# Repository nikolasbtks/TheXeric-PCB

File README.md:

# TheXeric-PCB

## Description

This project demonstrates a custom 2-layer PCB containing the ATmega-4809 microcontroller. This board can be used for embedded development applications using multiple peripherals.

## Components

1. Microcontroller: ATmega4809
   - 6 KB SRAM and 48 MB Flash
   - 20 MHz clock speed 
   
3. USB Connectivity:
   - USB Type-C for data and power 
   - USBLC6-2SC6 for ESD protection

4. Power Supply: LM3670MF-3.3 
   - Voltage regulator for stable 3.3V output
  
5. Headers:
   - UPDI header for debugging
   - GPIO, I2C, SPI and USART headers for external connections

6. Memory: AT24CS32-STUM
   - 32 Kbit of EEPROM storage
   - Non-volatile memory storage expansion

8. Sensor: TC1047xNB
   - Analog voltage output, propotional to temperature

## Disclaimer

This project is currently in **testing phase**. The provided documentation is shared for prototyping and learning purposes. If you choose to manufacture and use the board, please proceed with care, as it has not yet been fully validated.

## Schematic and PCB Design

The board was designed using KiCad. Files from the PCB design can be found in the **hardware** folder for board manufacture. This folder includes:

- PCB Schematic 
- PCB Layout
- Gerber files
- Assembly files

Below is a 3D render of the PCB design:

## How to Use

1. Power the board
   - Use a USB Type-C cable to power the board.
     
2. Microcontroller Programming:
   - Use Arduino IDE or any other platform to program the microcontroller.
   - Use a debugger with a UPDI header.

3. Peripheral Access
   - Use the GPIO, I2C, SPI and USART headers to connect peripherals.

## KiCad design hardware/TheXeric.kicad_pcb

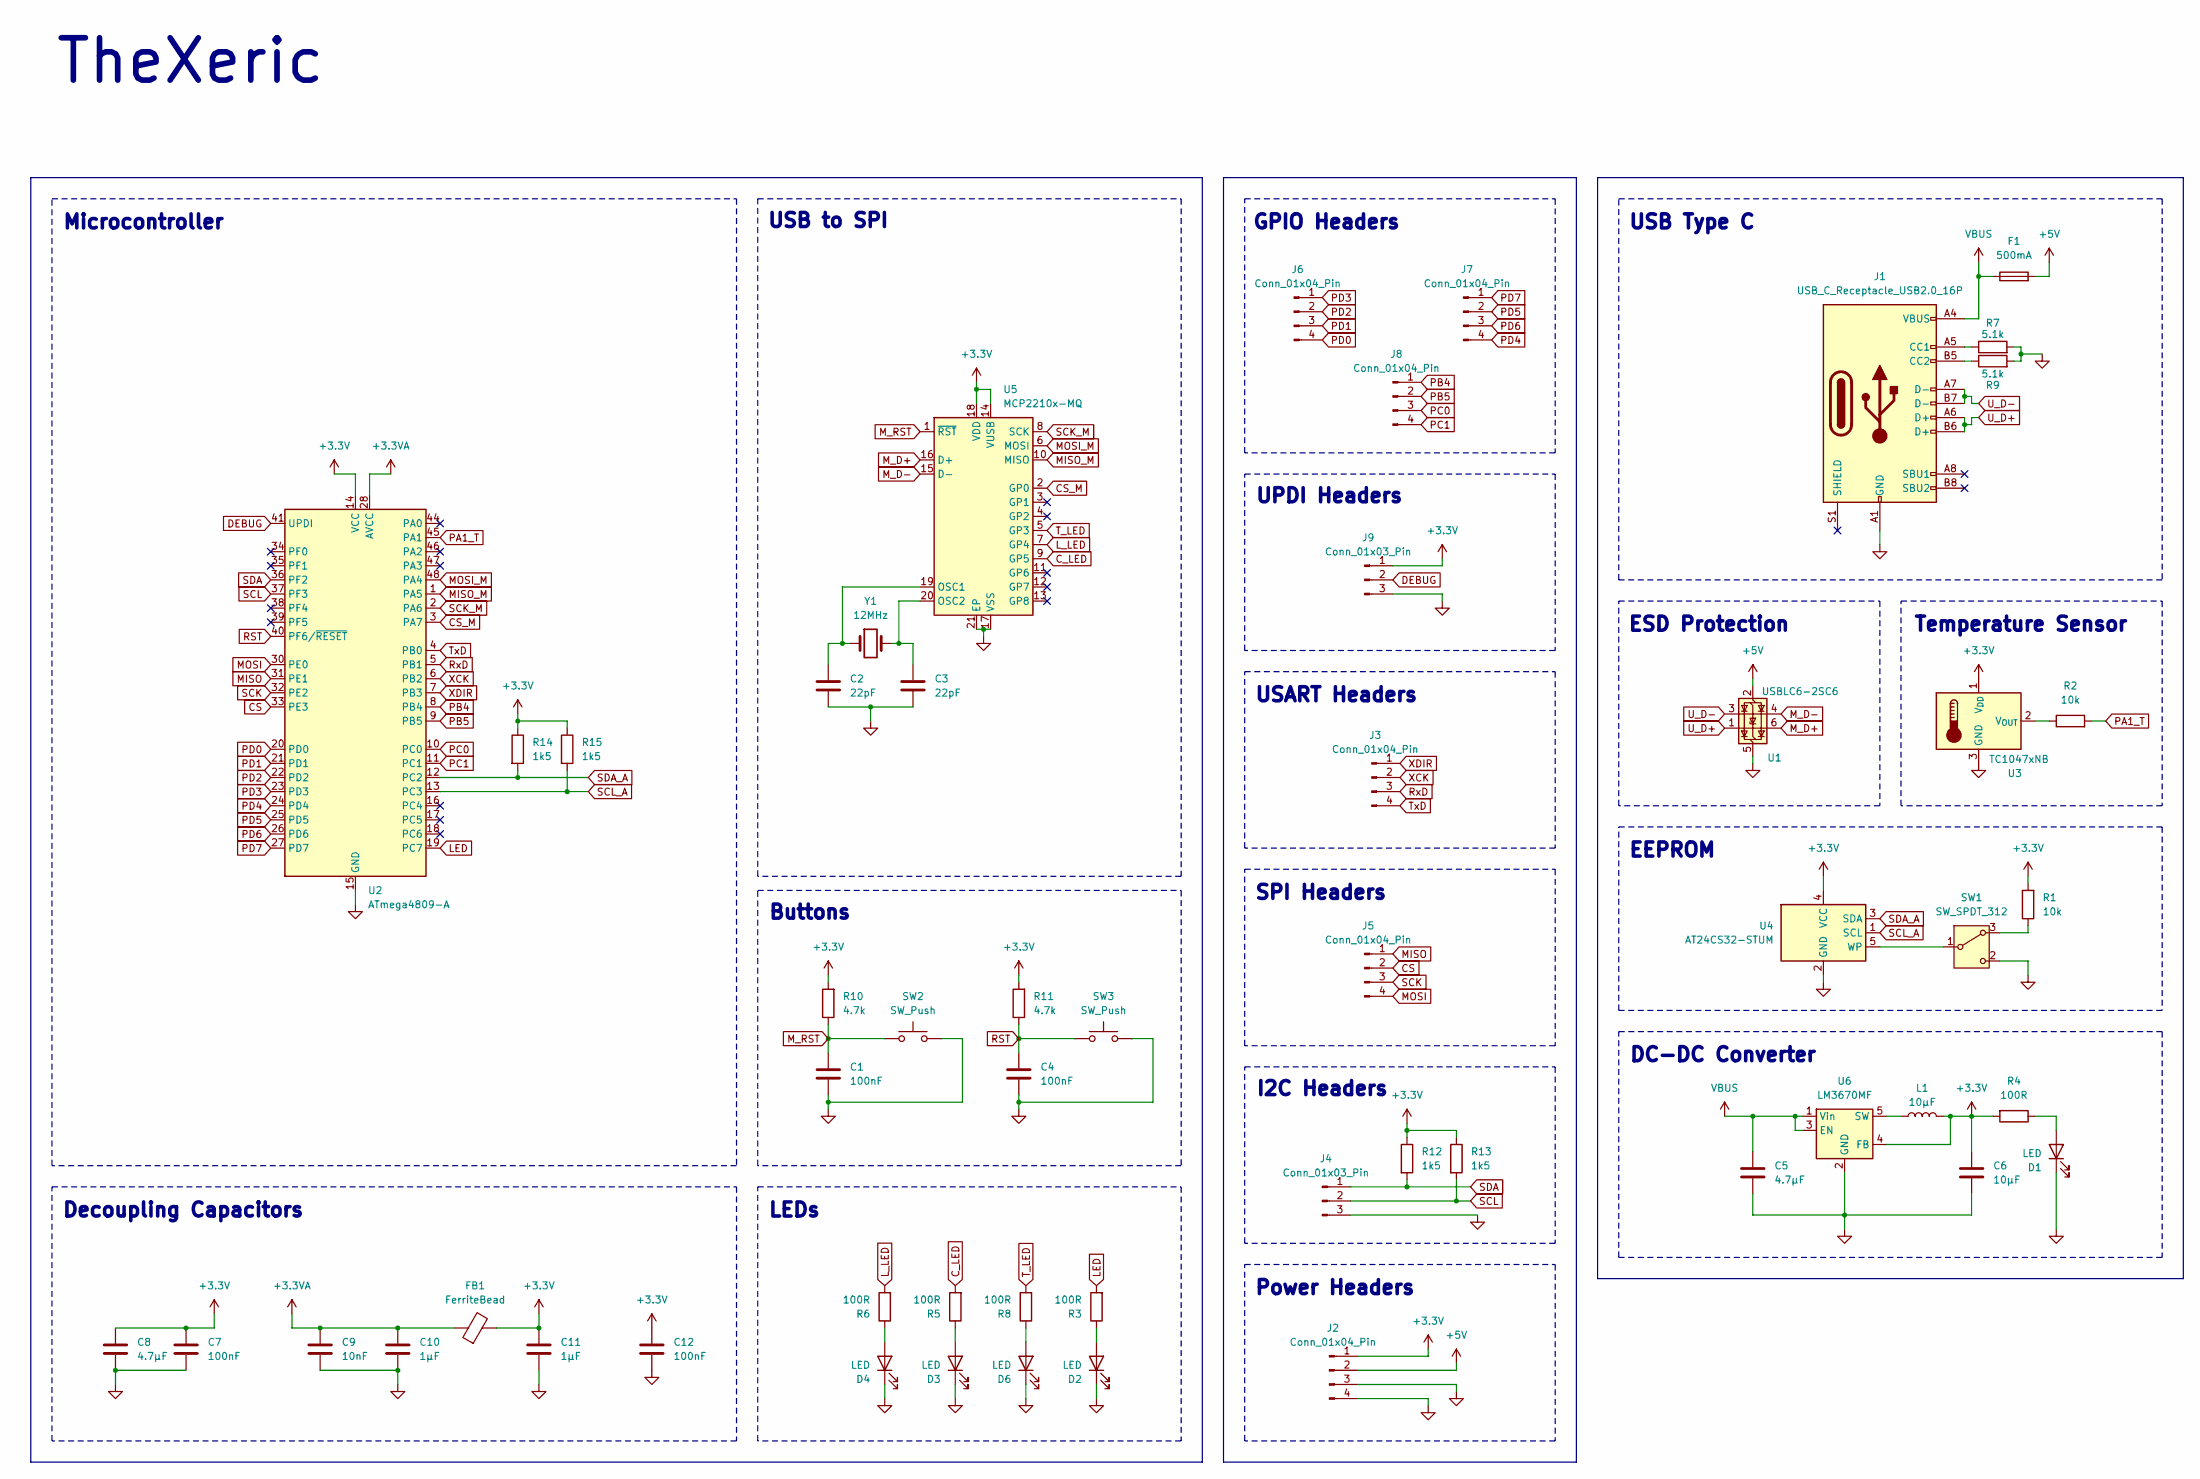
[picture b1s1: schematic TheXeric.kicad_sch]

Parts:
C1, C4, C7, C12: 100nF; C_0402_1005Metric
C2, C3: 22pF; C_0402_1005Metric
C5, C8: 4.7μF; C_0603_1608Metric
C6: 10μF; C_0603_1608Metric
C9: 10nF; C_0402_1005Metric
C10, C11: 1μF; C_0603_1608Metric
D1, D2, D3, D4, D6: LED; LED_0603_1608Metric
F1: 500mA; Fuse_0402_1005Metric
FB1: FerriteBead; L_0603_1608Metric
J1: USB_C_Receptacle_USB2.0_16P; USB_C_Receptacle_GCT_USB4105-xx-A_16P_TopMnt_Horizontal
J2, J3, J5, J6, J7, J8: Conn_01x04_Pin; PinHeader_1x04_P2.54mm_Vertical
J4, J9: Conn_01x03_Pin; PinHeader_1x03_P2.54mm_Vertical
L1: 10μF; L_0603_1608Metric
R1, R2: 10k; R_0402_1005Metric
R3, R4, R5, R6, R8: 100R; R_0603_1608Metric
R7, R9: 5.1k; R_0402_1005Metric
R10, R11: 4.7k; R_0402_1005Metric
R12, R13, R14, R15: 1k5; R_0402_1005Metric
SW1: SW_SPDT_312; SW_SPDT_PCM12
SW2, SW3: SW_Push; SW_SPST_B3U-1000P
U1: USBLC6-2SC6; SOT-23-6
U2: ATmega4809-A; TQFP-48_7x7mm_P0.5mm
U3: TC1047xNB; SOT-23
U4: AT24CS32-STUM; SOT-23-5
U5: MCP2210x-MQ; QFN-20-1EP_5x5mm_P0.65mm_EP3.35x3.35mm
U6: LM3670MF; TSOT-23-5
Y1: 12MHz; Crystal_SMD_3215-2Pin_3.2x1.5mm

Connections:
+3.3V: C6.1, C7.1, C8.1, C11.1, C12.1, FB1.2, J2.1, J9.1, L1.2, R1.2, R4.2, R10.2, R11.2, R12.1, R13.1, R14.1, R15.1, U2.14 (VCC), U2.42 (VCC), U3.1 (V_{DD}), U4.4 (VCC), U5.14 (VUSB), U5.18 (VDD), U6.4 (FB)
+3.3VA: C9.1, C10.1, FB1.1, U2.28 (AVCC)
+5V: F1.2, J2.2, U1.2 (GND)
CS: J5.2, U2.33 (PE3)
CS_M: U2.3 (PA7), U5.2 (GP0)
C_LED: R5.2, U5.9 (GP5)
DEBUG: J9.2, U2.41 (UPDI)
GND: C1.2, C2.2, C3.2, C4.2, C5.2, C6.2, C7.2, C8.2, C9.2, C10.2, C11.2, C12.2, D1.1 (K), D2.1 (K), D3.1 (K), D4.1 (K), D6.1 (K), J1.A1 (GND), J1.A12 (GND), J1.B1 (GND), J1.B12 (GND), J2.3, J2.4, J4.3, J9.3, R7.2, R9.2, SW1.2 (C), SW2.2, SW3.2, U1.5 (VBUS), U2.15 (GND), U2.29 (GND), U2.43 (GND), U3.3 (GND), U4.2 (GND), U5.17 (VSS), U5.21 (EP), U6.2 (GND)
LED: R3.2, U2.19 (PC7)
L_LED: R6.2, U5.7 (GP4)
MISO: J5.1, U2.31 (PE1)
MISO_M: U2.1 (PA5), U5.10 (MISO)
MOSI: J5.4, U2.30 (PE0)
MOSI_M: U2.48 (PA4), U5.6 (MOSI)
M_D+: U1.6 (I/O1), U5.16 (D+)
M_D-: U1.4 (I/O2), U5.15 (D-)
M_RST: C1.1, R10.1, SW2.1, U5.1 (~RST)
unnamed: D1.2 (A), R4.1
unnamed: D2.2 (A), R3.1
unnamed: D3.2 (A), R5.1
unnamed: D4.2 (A), R6.1
unnamed: D6.2 (A), R8.1
unnamed: J1.A5 (CC1), R7.1
unnamed: J1.B5 (CC2), R9.1
unnamed: R1.1, SW1.3 (A)
unnamed: SW1.1 (B), U4.5 (WP)
unnamed: R2.1, U3.2 (V_{OUT})
unnamed: C2.1, U5.19 (OSC1), Y1.1
unnamed: C3.1, U5.20 (OSC2), Y1.2
unnamed: L1.1, U6.5 (SW)
PA1_T: R2.2, U2.45 (PA1)
PB4: J8.1, U2.8 (PB4)
PB5: J8.2, U2.9 (PB5)
PC0: J8.3, U2.10 (PC0)
PC1: J8.4, U2.11 (PC1)
PD0: J6.4, U2.20 (PD0)
PD1: J6.3, U2.21 (PD1)
PD2: J6.2, U2.22 (PD2)
PD3: J6.1, U2.23 (PD3)
PD4: J7.4, U2.24 (PD4)
PD5: J7.2, U2.25 (PD5)
PD6: J7.3, U2.26 (PD6)
PD7: J7.1, U2.27 (PD7)
RST: C4.1, R11.1, SW3.1, U2.40 (PF6/~RESET)
RxD: J3.3, U2.5 (PB1)
SCK: J5.3, U2.32 (PE2)
SCK_M: U2.2 (PA6), U5.8 (SCK)
SCL: J4.2, R13.2, U2.37 (PF3)
SCL_A: R15.2, U2.13 (PC3), U4.1 (SCL)
SDA: J4.1, R12.2, U2.36 (PF2)
SDA_A: R14.2, U2.12 (PC2), U4.3 (SDA)
T_LED: R8.2, U5.5 (GP3)
TxD: J3.4, U2.4 (PB0)
U_D+: J1.A6 (D+), J1.B6 (D+), U1.1 (I/O1)
U_D-: J1.A7 (D-), J1.B7 (D-), U1.3 (I/O2)
VBUS: C5.1, F1.1, J1.A4 (VBUS), J1.A9 (VBUS), J1.B4 (VBUS), J1.B9 (VBUS), U6.1 (Vin), U6.3 (EN)
XCK: J3.2, U2.6 (PB2)
XDIR: J3.1, U2.7 (PB3)

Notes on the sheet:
Microcontroller
EEPROM
USART Headers
LEDs
USB Type C
Power Headers
Buttons
UPDI Headers
GPIO Headers
TheXeric
I2C Headers
USB to SPI
SPI Headers
DC-DC Converter
Decoupling Capacitors
ESD Protection
Temperature Sensor

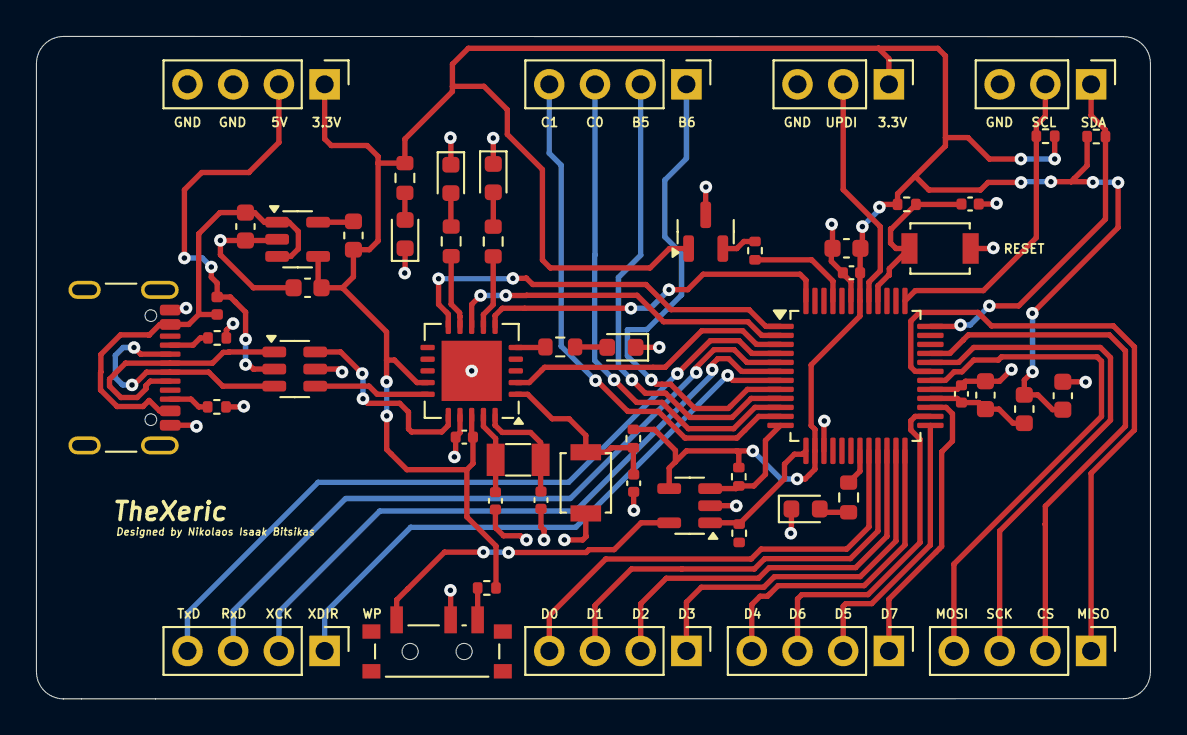
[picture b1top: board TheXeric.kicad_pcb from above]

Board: 2 copper layers, 61.9 x 36.8 mm, 54 parts (0 on the bottom side), 58 nets.
